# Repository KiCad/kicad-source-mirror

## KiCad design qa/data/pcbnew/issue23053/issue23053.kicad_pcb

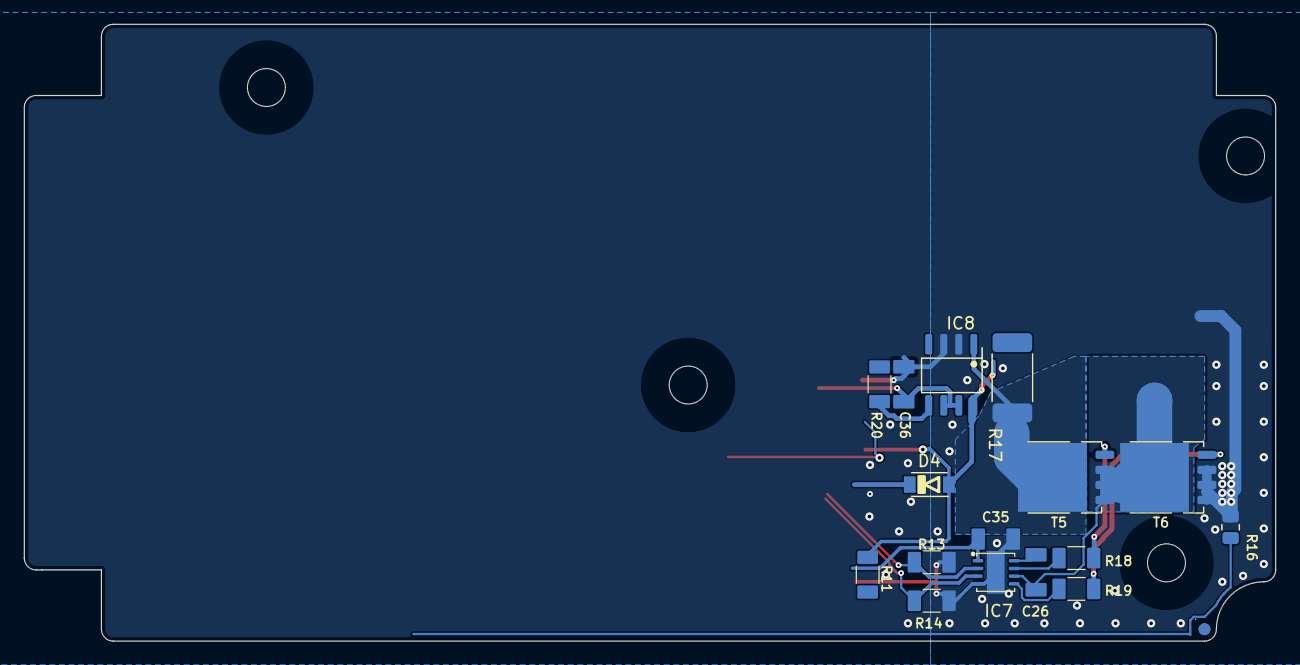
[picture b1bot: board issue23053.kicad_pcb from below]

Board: 2 copper layers, 105.5 x 52.0 mm, 21 parts (16 on the bottom side), 14 nets.

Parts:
C26, C35: 10uF/50V; C_1206_3216Metric
C36: 100nF; C_1206_3216Metric
D4: PMEG6010CEGW; D_IBF_SOD123
H2, H3, H4, H5: MountingHole; MountingHole_3.2mm_M3_4mm-iso
IC7: HIP2103; DFN-8-1EP_3x3mm_P0.65mm_EP1.2x3.6mm
IC8: AD8418AWBRZ; SO-8_3.9x4.9mm_P1.27mm_IBF
Mark3: Mark; MARK_round_1.0mm
R11, R13, R14: 10k; R_1206_3216Metric
R16: NCP21XV103J03RA; R_0805_2012Metric
R17: 0,005R; R_2512_6332Metric
R18, R19: 3,3R; R_1206_3216Metric
R20: 1k; R_1206_3216Metric
T5, T6: BSC028N06N; PG-TDSON-8_GDS

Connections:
+3V3: C36.1, IC8.6 (vs), IC8.7 (ref1)
+5V: C35.1, IC7.1 (Vdd)
+Vbat: D4.2 (A), IC8.8 (+in), R11.1, R17.1
/Leistungsteil_Mosfet/UZ: IC8.1 (-in), R17.2, T5.D
/Leistungsteil_Mosfet/bruecke_mitte: C26.2, IC7.6 (HS), T5.S, T6.D
GND: C35.2, C36.2, IC7.4 (Vss), IC7.9 (Vss), IC8.2 (gnd), IC8.3 (ref2), R13.2, R14.2, R16.2, T6.S
unnamed: C26.1, IC7.8 (HB)
unnamed: IC7.7 (HO), R18.1
unnamed: IC7.5 (LO), R19.1
unnamed: IC8.5 (out), R20.1
unnamed: R18.2, T5.G
unnamed: R19.2, T6.G
TIM8_CH1: IC7.2 (HI), R13.1
TIM8_CH1N: IC7.3 (LI), R14.1

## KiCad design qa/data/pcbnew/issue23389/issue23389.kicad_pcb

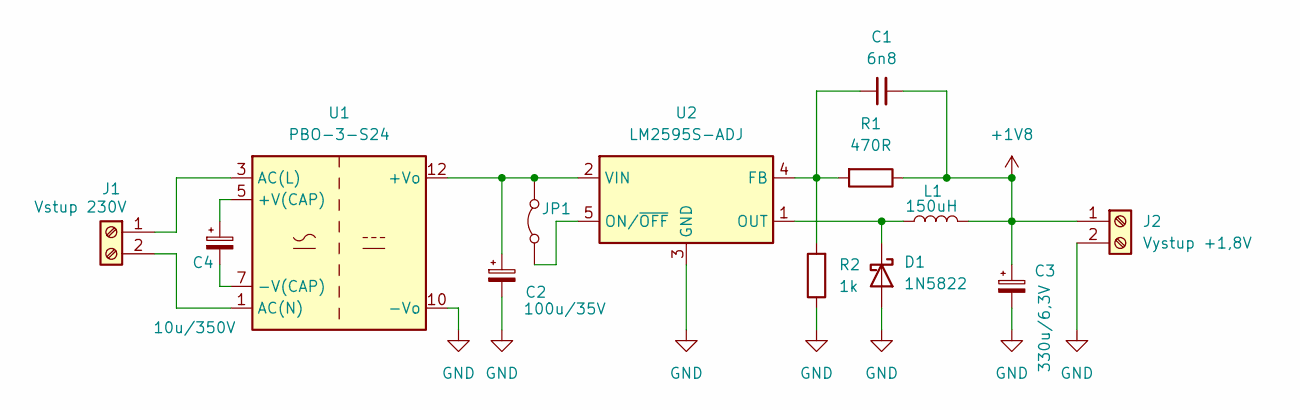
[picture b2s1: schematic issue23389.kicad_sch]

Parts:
C1: 6n8; C_1206_3216Metric_Pad1.33x1.80mm_HandSolder
C2: 100u/35V; CP_Radial_D8.0mm_P3.50mm
C3: 330u/6,3V; CP_Radial_D6.3mm_P2.50mm
C4: 10u/350V; CP_Radial_D8.0mm_P3.50mm
D1: 1N5822; D_DO-201AD_P15.24mm_Horizontal
J1: Vstup 230V; Altech_AK100_1x02_P5.00mm
J2: Vystup +1,8V; Altech_AK100_1x02_P5.00mm
JP1: Jumper_2_Bridged; TestPoint_2Pads_Pitch2.54mm_Drill0.8mm
L1: 150uH; L_Radial_D12.0mm_P10.00mm_Neosid_SD12_style1
R1: 470R; R_1206_3216Metric_Pad1.30x1.75mm_HandSolder
R2: 1k; R_1206_3216Metric_Pad1.30x1.75mm_HandSolder
U1: PBO-3-S24; Converter_ACDC_CUI_PBO-3-Sxx_THT_Vertical
U2: LM2595S-ADJ; TO-263-5_TabPin3

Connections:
+1V8: C1.2, C3.1, J2.1, L1.2, R1.1
GND: C2.2, C3.2, D1.2 (A), J2.2, R2.1, U1.10 (-Vo), U2.3 (GND)
unnamed: D1.1 (K), L1.1, U2.1 (OUT)
unnamed: J1.1, U1.3 (AC(L))
unnamed: J1.2, U1.1 (AC(N))
unnamed: JP1.1 (A), U2.5 (ON/~OFF)
unnamed: C2.1, JP1.2 (B), U1.12 (+Vo), U2.2 (VIN)
unnamed: C4.1, U1.5 (+V(CAP))
unnamed: C4.2, U1.7 (-V(CAP))
unnamed: C1.1, R1.2, R2.2, U2.4 (FB)

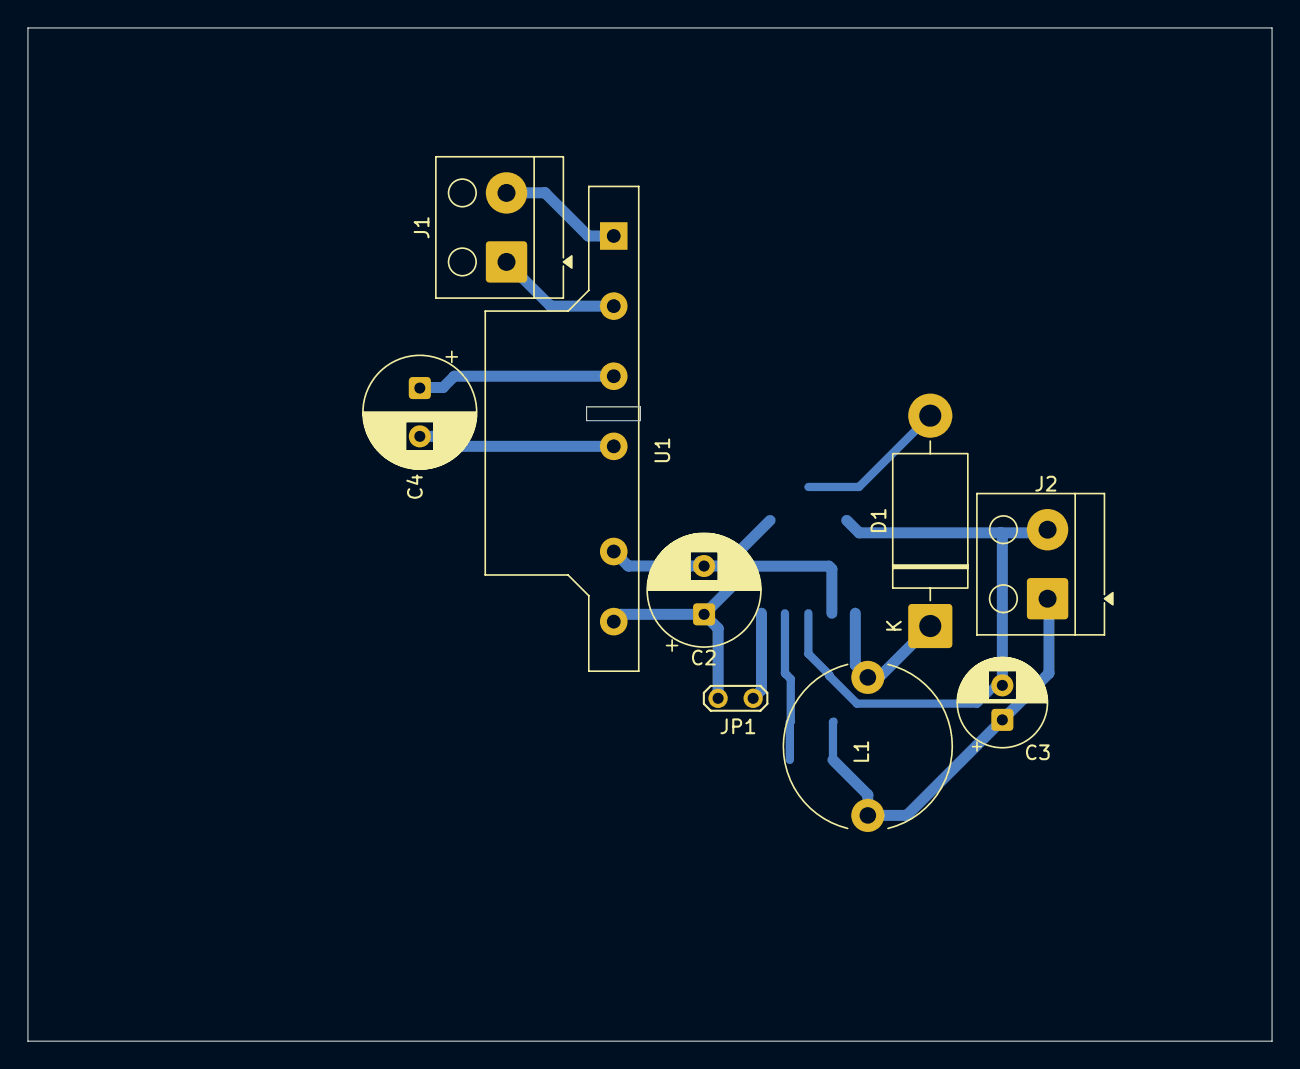
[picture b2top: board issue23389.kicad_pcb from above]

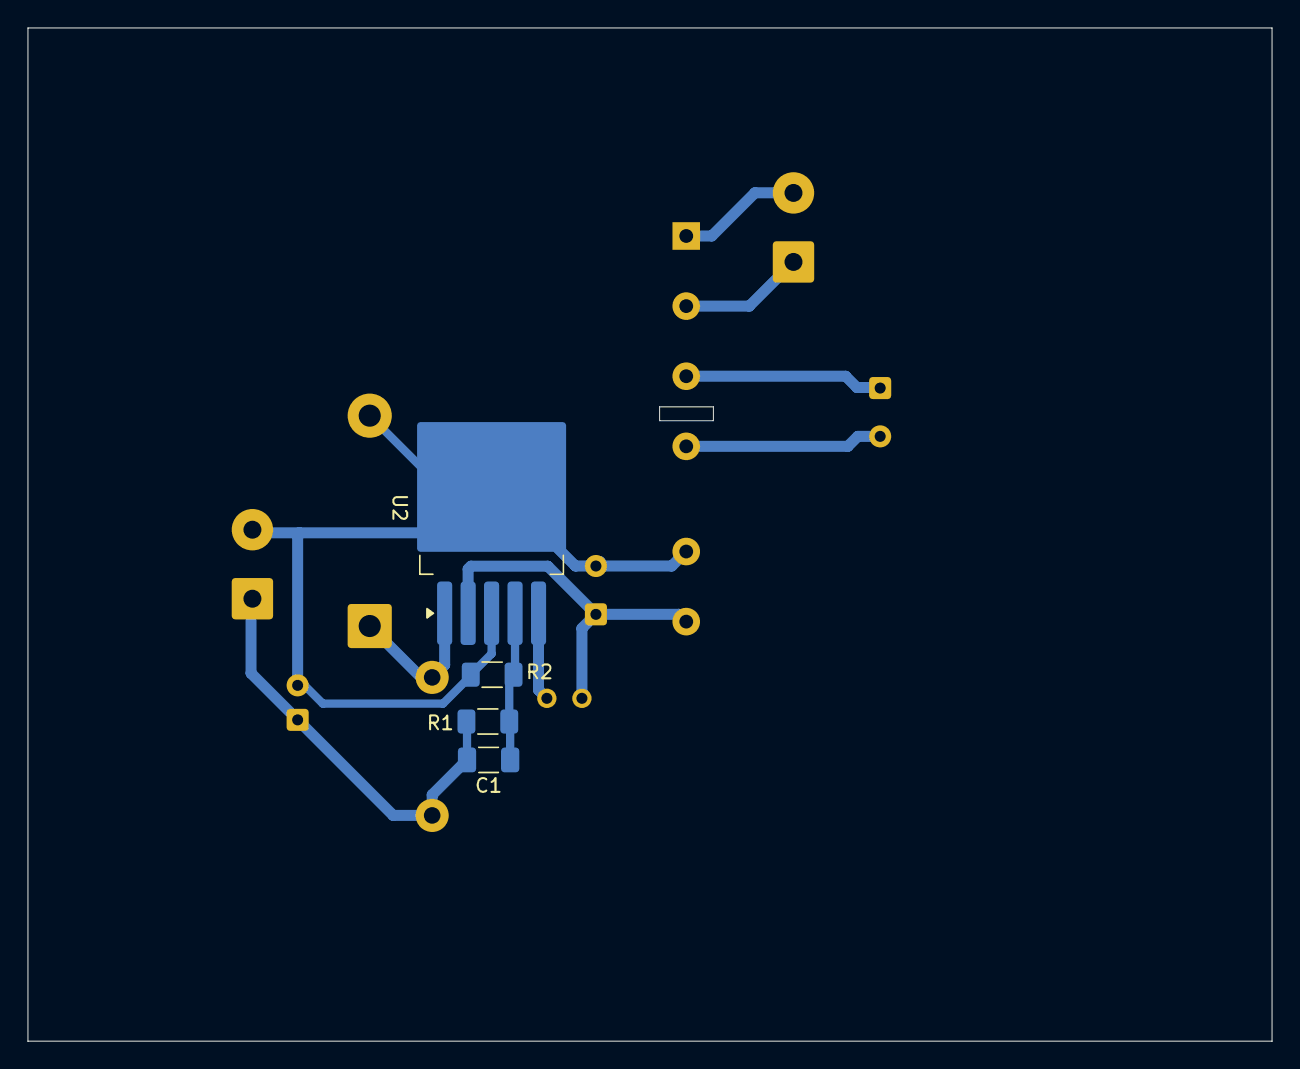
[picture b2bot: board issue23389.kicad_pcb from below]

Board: 2 copper layers, 90.1 x 73.4 mm, 13 parts (4 on the bottom side), 10 nets.
